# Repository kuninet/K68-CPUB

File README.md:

# K68-CPUB

## 注意!! REV1基板はバグ多数です。REV2基板を使ってください。

* https://kuninet.org/2021/08/16/mc6800-cpu%e3%83%9c%e3%83%bc%e3%83%892-%e3%83%97%e3%83%aa%e3%83%b3%e3%83%88%e5%9f%ba%e6%9d%bf%e5%8c%96/

## 概要

* MC6800を使ったマイコンボードです。
  * MIKBUGオリジナルROMで動きます。
  * PIA MC6821/20をつかったシリアル通信が可能で、300bpsです。
* 10cm x 10cm サイズのプリント基板データがあります。基板固定穴は秋月電子Bサイズユニバーサル基板に合わせてあります。

## 部品・回路図など

* 部品表は以下のディレクトリに入っています。
  * KiCAD/K68-CPUB_BOM/BOM.csv
* 回路図PDFは以下のディレクトリに入っています。
  * KiCAD/K68-CPUB.pdf

## スイッチ、調整方法について
### スイッチ
* 基板上に以下のスイッチがあります。

| 記号 | スイッチ名     | 機能                                          |
| ---- | -------------- | --------------------------------------------- |
| SW1  | 電源スイッチ   | 電源のOFF/ON                                  |
| SW2  | エコーバックSW | 通常はONにして使用してください。              |
| SW3  | ボーレートSW   | 110bps/300bpsの切り替え。<br>ONで300bpsです。 |

### CPUクロック調整、シリアルクロック調整
#### CPUクロック
* 部品を組み付けたのち 74LS123のそばのRV1、RV2を調整して 700kHz～1MHzぐらいに調整してください。
* ※テスタ等の周波数カウンタをGNDとMC6800 CPUのPH1/PH2端子につないで調整してください。

### シリアルクロック
* 部品を組み付けたのち RV3を調整してください。300bpsにする場合は150Hzになるように調整してください。
* ※テスタ等の周波数カウンタをGNDとMC14536の13番ピンにつないで調整してください。

## 参考

* 書籍「マイコンの作り方・使い方」 啓学出版

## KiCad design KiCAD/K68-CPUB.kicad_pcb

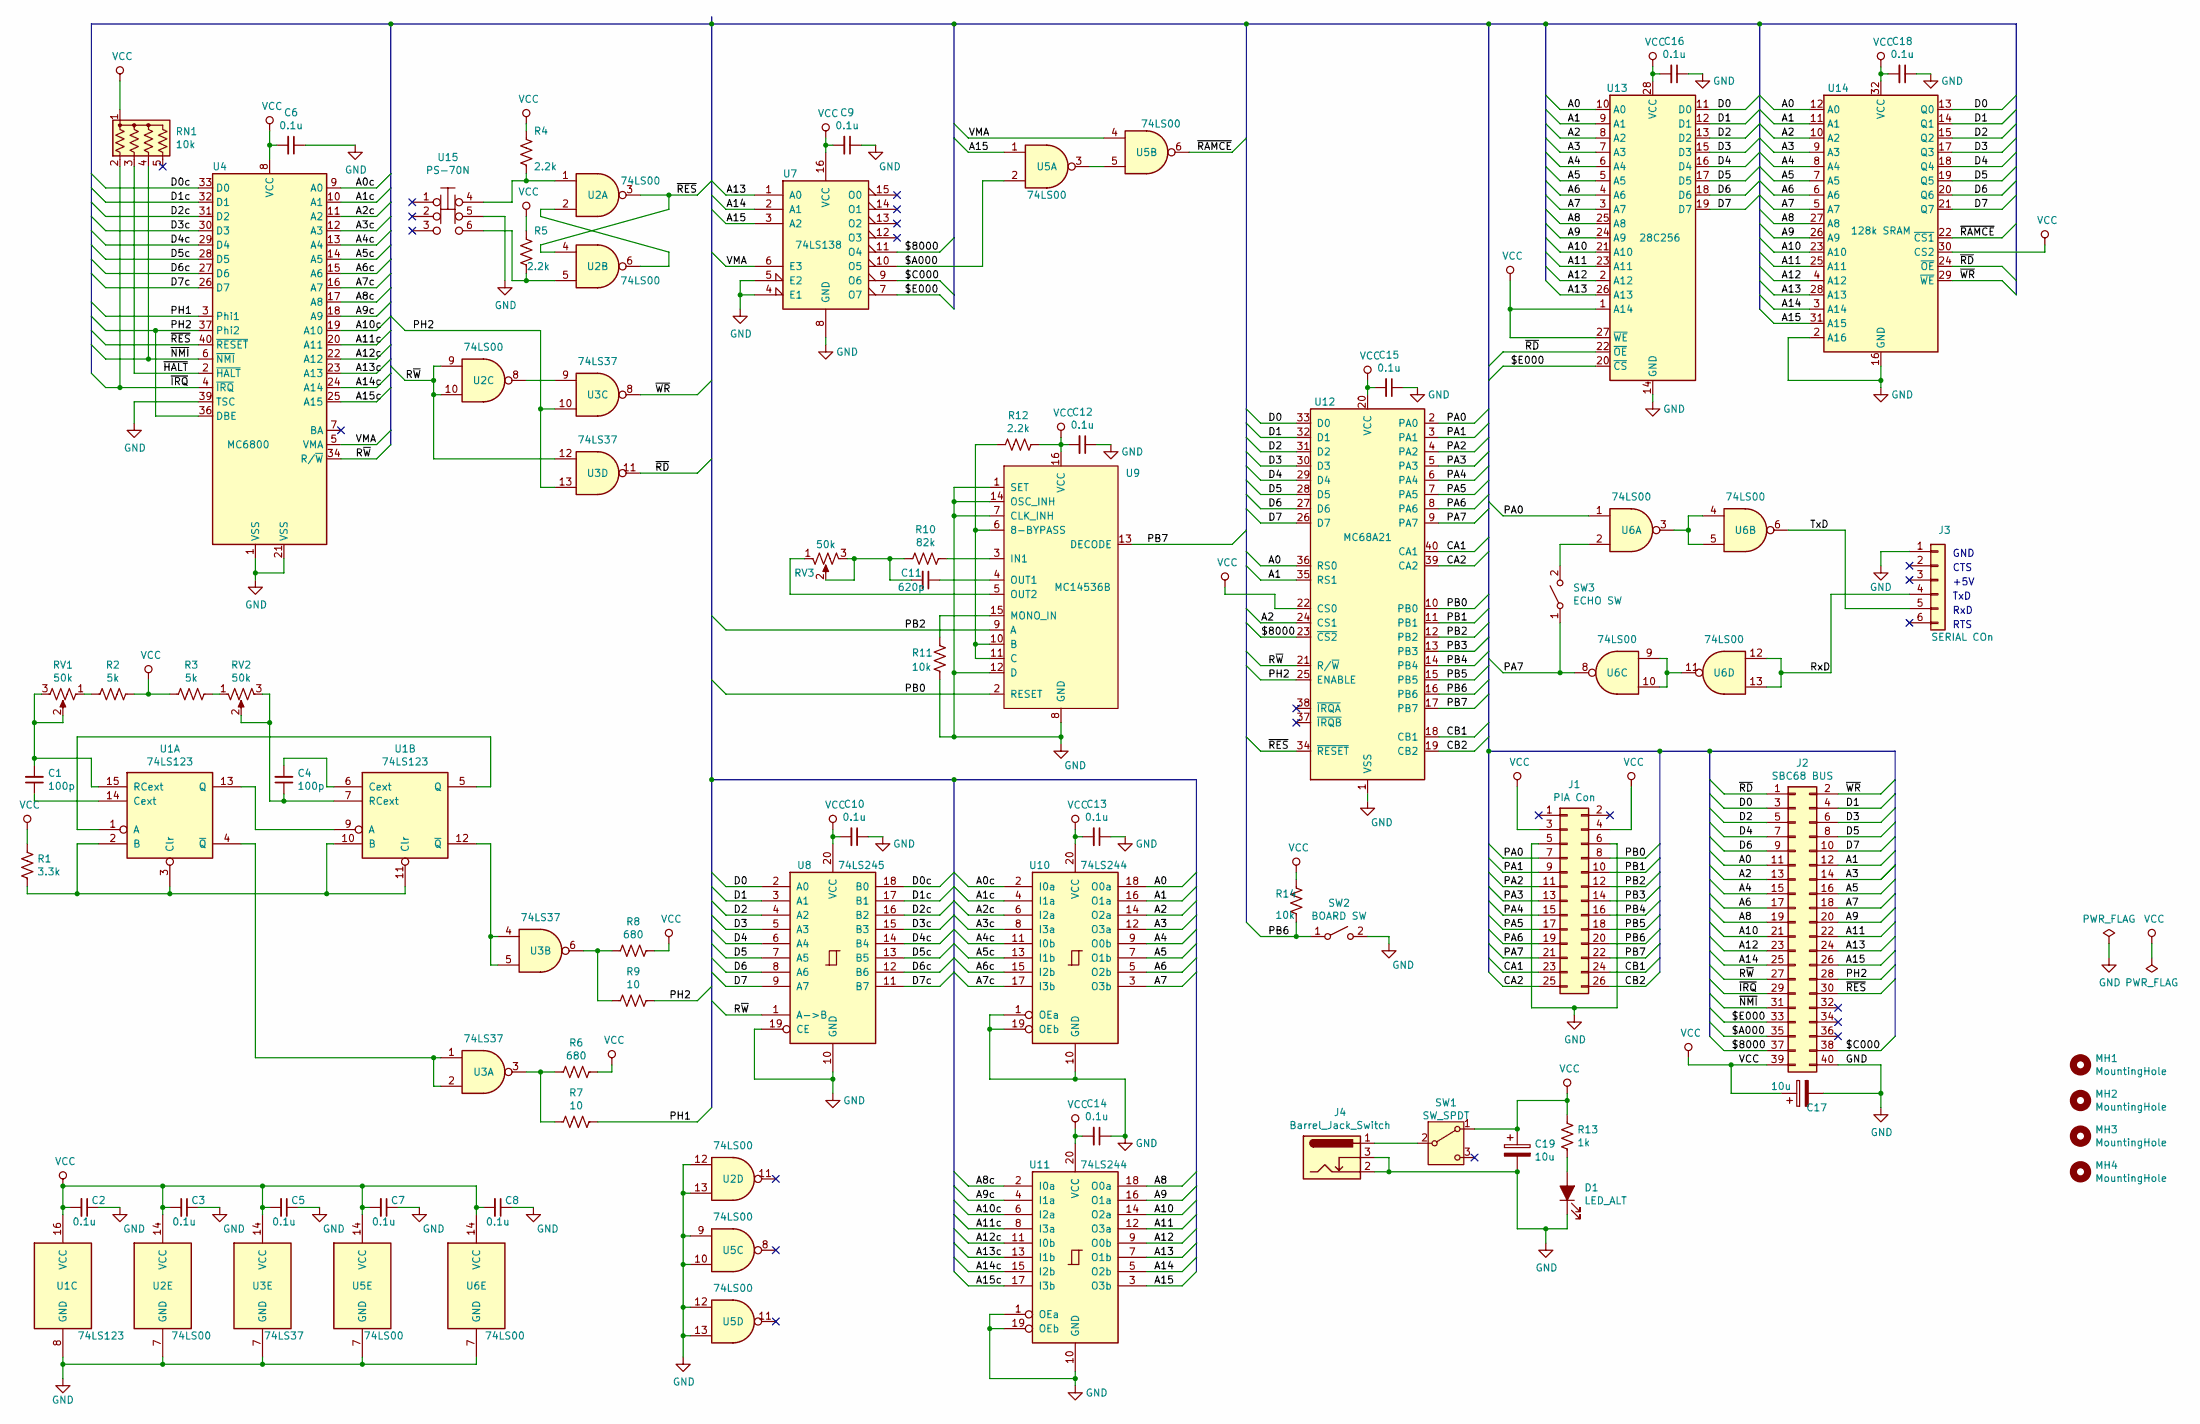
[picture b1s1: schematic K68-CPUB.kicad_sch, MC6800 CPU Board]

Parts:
C1, C4: 100p; C_Disc_D4.3mm_W1.9mm_P5.00mm
C2, C3, C5, C6, C7, C8, C9, C10, C12, C13, C14, C15, C16, C18: 0.1u; C_Disc_D3.0mm_W1.6mm_P2.50mm
C11: 620p; C_Disc_D4.3mm_W1.9mm_P5.00mm
C17, C19: 10u; CP_Radial_D5.0mm_P2.50mm
D1: LED_ALT; LED_D3.0mm
J1: PIA Con; PinHeader_2x13_P2.54mm_Horizontal
J2: SBC68 BUS; PinHeader_2x20_P2.54mm_Horizontal
J3: SERIAL COn; PinHeader_1x06_P2.54mm_Horizontal
J4: Barrel_Jack_Switch; BarrelJack_Horizontal
MH1, MH2, MH3, MH4: MountingHole; MountingHole_3.2mm_M3
R1: 3.3k; R_Axial_DIN0207_L6.3mm_D2.5mm_P10.16mm_Horizontal
R2, R3: 5k; R_Axial_DIN0207_L6.3mm_D2.5mm_P10.16mm_Horizontal
R4, R5, R12: 2.2k; R_Axial_DIN0207_L6.3mm_D2.5mm_P10.16mm_Horizontal
R6, R8: 680; R_Axial_DIN0207_L6.3mm_D2.5mm_P10.16mm_Horizontal
R7, R9: 10; R_Axial_DIN0207_L6.3mm_D2.5mm_P10.16mm_Horizontal
R10: 82k; R_Axial_DIN0207_L6.3mm_D2.5mm_P10.16mm_Horizontal
R11, R14: 10k; R_Axial_DIN0207_L6.3mm_D2.5mm_P10.16mm_Horizontal
R13: 1k; R_Axial_DIN0207_L6.3mm_D2.5mm_P10.16mm_Horizontal
RN1: 10k; R_Array_SIP5
RV1, RV2, RV3: 50k; Potentiometer_Bourns_3386P_Vertical
SW1: SW_SPDT; PinHeader_1x03_P2.54mm_Vertical
SW2: BOARD SW; PinHeader_1x03_P2.54mm_Vertical
SW3: ECHO SW; PinHeader_1x03_P2.54mm_Vertical
U1: 74LS123; DIP-16_W7.62mm_Socket
U2, U5, U6: 74LS00; DIP-14_W7.62mm_Socket
U3: 74LS37; DIP-14_W7.62mm_Socket
U4: MC6800; DIP-40_W15.24mm_Socket
U7: 74LS138; DIP-16_W7.62mm_Socket
U8: 74LS245; DIP-20_W7.62mm_Socket
U9: MC14536B; DIP-16_W7.62mm_Socket
U10, U11: 74LS244; DIP-20_W7.62mm_Socket
U12: MC68A21; DIP-40_W15.24mm_Socket
U13: 28C256; DIP-28_W15.24mm_Socket
U14: 128k SRAM; DIP-32_W15.24mm_Socket
U15: PS-70N; SW_PUSH_PS-70N

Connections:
/$8000: J2.37, U7.11 (O4), U12.23 (~CS2)
/$A000: J2.35, U5.2, U7.10 (O5)
/$C000: J2.38, U7.9 (O6)
/$E000: J2.33, U7.7 (O7), U13.20 (~CS)
/A0: J2.11, U10.18 (O0a), U12.36 (RS0), U13.10 (A0), U14.12 (A0)
/A0c: U4.9 (A0), U10.2 (I0a)
/A1: J2.12, U10.16 (O1a), U12.35 (RS1), U13.9 (A1), U14.11 (A1)
/A1c: U4.10 (A1), U10.4 (I1a)
/A2: J2.13, U10.14 (O2a), U12.24 (CS1), U13.8 (A2), U14.10 (A2)
/A2c: U4.11 (A2), U10.6 (I2a)
/A3: J2.14, U10.12 (O3a), U13.7 (A3), U14.9 (A3)
/A3c: U4.12 (A3), U10.8 (I3a)
/A4: J2.15, U10.9 (O0b), U13.6 (A4), U14.8 (A4)
/A4c: U4.13 (A4), U10.11 (I0b)
/A5: J2.16, U10.7 (O1b), U13.5 (A5), U14.7 (A5)
/A5c: U4.14 (A5), U10.13 (I1b)
/A6: J2.17, U10.5 (O2b), U13.4 (A6), U14.6 (A6)
/A6c: U4.15 (A6), U10.15 (I2b)
/A7: J2.18, U10.3 (O3b), U13.3 (A7), U14.5 (A7)
/A7c: U4.16 (A7), U10.17 (I3b)
/A8: J2.19, U11.18 (O0a), U13.25 (A8), U14.27 (A8)
/A8c: U4.17 (A8), U11.2 (I0a)
/A9: J2.20, U11.16 (O1a), U13.24 (A9), U14.26 (A9)
/A9c: U4.18 (A9), U11.4 (I1a)
/A10: J2.21, U11.14 (O2a), U13.21 (A10), U14.23 (A10)
/A10c: U4.19 (A10), U11.6 (I2a)
/A11: J2.22, U11.12 (O3a), U13.23 (A11), U14.25 (A11)
/A11c: U4.20 (A11), U11.8 (I3a)
/A12: J2.23, U11.9 (O0b), U13.2 (A12), U14.4 (A12)
/A12c: U4.22 (A12), U11.11 (I0b)
/A13: J2.24, U7.1 (A0), U11.7 (O1b), U13.26 (A13), U14.28 (A13)
/A13c: U4.23 (A13), U11.13 (I1b)
/A14: J2.25, U7.2 (A1), U11.5 (O2b), U14.3 (A14)
/A14c: U4.24 (A14), U11.15 (I2b)
/A15: J2.26, U5.1, U7.3 (A2), U11.3 (O3b), U14.31 (A15)
/A15c: U4.25 (A15), U11.17 (I3b)
/CA1: J1.23, U12.40 (CA1)
/CA2: J1.25, U12.39 (CA2)
/CB1: J1.24, U12.18 (CB1)
/CB2: J1.26, U12.19 (CB2)
/D0: J2.3, U8.2 (A0), U12.33 (D0), U13.11 (D0), U14.13 (Q0)
/D0c: U4.33 (D0), U8.18 (B0)
/D1: J2.4, U8.3 (A1), U12.32 (D1), U13.12 (D1), U14.14 (Q1)
/D1c: U4.32 (D1), U8.17 (B1)
/D2: J2.5, U8.4 (A2), U12.31 (D2), U13.13 (D2), U14.15 (Q2)
/D2c: U4.31 (D2), U8.16 (B2)
/D3: J2.6, U8.5 (A3), U12.30 (D3), U13.15 (D3), U14.17 (Q3)
/D3c: U4.30 (D3), U8.15 (B3)
/D4: J2.7, U8.6 (A4), U12.29 (D4), U13.16 (D4), U14.18 (Q4)
/D4c: U4.29 (D4), U8.14 (B4)
/D5: J2.8, U8.7 (A5), U12.28 (D5), U13.17 (D5), U14.19 (Q5)
/D5c: U4.28 (D5), U8.13 (B5)
/D6: J2.9, U8.8 (A6), U12.27 (D6), U13.18 (D6), U14.20 (Q6)
/D6c: U4.27 (D6), U8.12 (B6)
/D7: J2.10, U8.9 (A7), U12.26 (D7), U13.19 (D7), U14.21 (Q7)
/D7c: U4.26 (D7), U8.11 (B7)
/PA0: J1.7, U6.1, U12.2 (PA0)
/PA1: J1.9, U12.3 (PA1)
/PA2: J1.11, U12.4 (PA2)
/PA3: J1.13, U12.5 (PA3)
/PA4: J1.15, U12.6 (PA4)
/PA5: J1.17, U12.7 (PA5)
/PA6: J1.19, U12.8 (PA6)
/PA7: J1.21, SW3.1 (A), U6.8, U12.9 (PA7)
/PB0: J1.8, U9.2 (RESET), U12.10 (PB0)
/PB1: J1.10, U12.11 (PB1)
/PB2: J1.12, U9.9 (A), U12.12 (PB2)
/PB3: J1.14, U12.13 (PB3)
/PB4: J1.16, U12.14 (PB4)
/PB5: J1.18, U12.15 (PB5)
/PB6: J1.20, R14.1, SW2.1 (A), U12.16 (PB6)
/PB7: J1.22, U9.13 (DECODE), U12.17 (PB7)
/PH1: R7.1, U4.3 (Phi1)
/PH2: J2.28, R9.1, U3.10, U3.13, U4.36 (DBE), U4.37 (Phi2), U12.25 (ENABLE)
/RxD: J3.4, U6.12, U6.13
/R~W: J2.27, U2.9, U2.10, U3.12, U4.34 (R/~W), U8.1 (A->B), U12.21 (R/~W)
/TxD: J3.5, U6.6
/VMA: U4.5 (VMA), U5.4, U7.6 (E3)
/~HALT: RN1.3 (R2), U4.2 (~HALT)
/~IRQ: J2.29, RN1.2 (R1), U4.4 (~IRQ)
/~NMI: J2.31, RN1.4 (R3), U4.6 (~NMI)
/~RAMCE: U5.6, U14.22 (~CS1)
/~RD: J2.1, U3.11, U13.22 (~OE), U14.24 (~OE)
/~RES: J2.30, U2.3, U2.4, U4.40 (~RESET), U12.34 (~RESET)
/~WR: J2.2, U3.8, U14.29 (~WE)
GND: C2.1, C3.1, C5.1, C6.1, C7.1, C8.1, C9.1, C10.1, C12.1, C13.1, C14.1, C15.1, C16.1, C17.2, C18.1, C19.2, D1.1 (K), J1.5, J1.6, J2.40, J3.1, J4.2, J4.3, R11.1, SW2.2 (B), U1.8 (GND), U2.7 (GND), U2.12, U2.13, U3.7 (GND), U4.1 (VSS), U4.21 (VSS), U4.39 (TSC), U5.7 (GND), U5.9, U5.10, U5.12, U5.13, U6.7 (GND), U7.4 (E1), U7.5 (E2), U7.8 (GND), U8.10 (GND), U8.19 (CE), U9.1 (SET), U9.7 (CLK_INH), U9.8 (GND), U9.12 (D), U9.14 (OSC_INH), U10.1 (OEa), U10.10 (GND), U10.19 (OEb), U11.1 (OEa), U11.10 (GND), U11.19 (OEb), U12.1 (VSS), U13.14 (GND), U14.2 (A16), U14.16 (GND), U15.5
unnamed: C11.2, R10.2, RV3.2, RV3.3
unnamed: D1.2 (A), R13.2
unnamed: R2.2, RV1.1
unnamed: R3.1, RV2.1
unnamed: R4.2, U2.1, U15.4
unnamed: R5.2, U2.5, U15.6
unnamed: R6.2, R7.2, U3.3
unnamed: R8.2, R9.2, U3.6
unnamed: J4.1, SW1.2 (B)
unnamed: SW3.2 (B), U6.2
unnamed: U1.1 (A), U1.5 (Q)
unnamed: R1.2, U1.2 (B), U1.3 (Clr), U1.10 (B), U1.11 (Clr)
unnamed: C1.1, U1.14 (Cext)
unnamed: U1.9 (A), U1.13 (Q)
unnamed: C1.2, RV1.2, RV1.3, U1.15 (RCext)
unnamed: U1.4 (~Q), U3.1, U3.2
unnamed: C4.2, U1.6 (Cext)
unnamed: C4.1, RV2.2, RV2.3, U1.7 (RCext)
unnamed: U1.12 (~Q), U3.4, U3.5
unnamed: U2.2, U2.6
unnamed: U2.8, U3.9
unnamed: U5.3, U5.5
unnamed: U6.3, U6.4, U6.5
unnamed: U6.9, U6.10, U6.11
unnamed: R12.2, U9.6 (8-BYPASS), U9.10 (B), U9.11 (C)
unnamed: R10.1, U9.3 (IN1)
unnamed: R11.2, U9.15 (MONO_IN)
unnamed: C11.1, U9.4 (OUT1)
unnamed: RV3.1, U9.5 (OUT2)
VCC: C2.2, C3.2, C5.2, C6.2, C7.2, C8.2, C9.2, C10.2, C12.2, C13.2, C14.2, C15.2, C16.2, C17.1, C18.2, C19.1, J1.3, J1.4, J2.39, R1.1, R2.1, R3.2, R4.1, R5.1, R6.1, R8.1, R12.1, R13.1, R14.2, RN1.1 (common), SW1.1 (A), U1.16 (VCC), U2.14 (VCC), U3.14 (VCC), U4.8 (VCC), U5.14 (VCC), U6.14 (VCC), U7.16 (VCC), U8.20 (VCC), U9.16 (VCC), U10.20 (VCC), U11.20 (VCC), U12.20 (VCC), U12.22 (CS0), U13.1 (A14), U13.27 (~WE), U13.28 (VCC), U14.30 (CS2), U14.32 (VCC)

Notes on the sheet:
RxD
+5V
GND
TxD
CTS
RTS

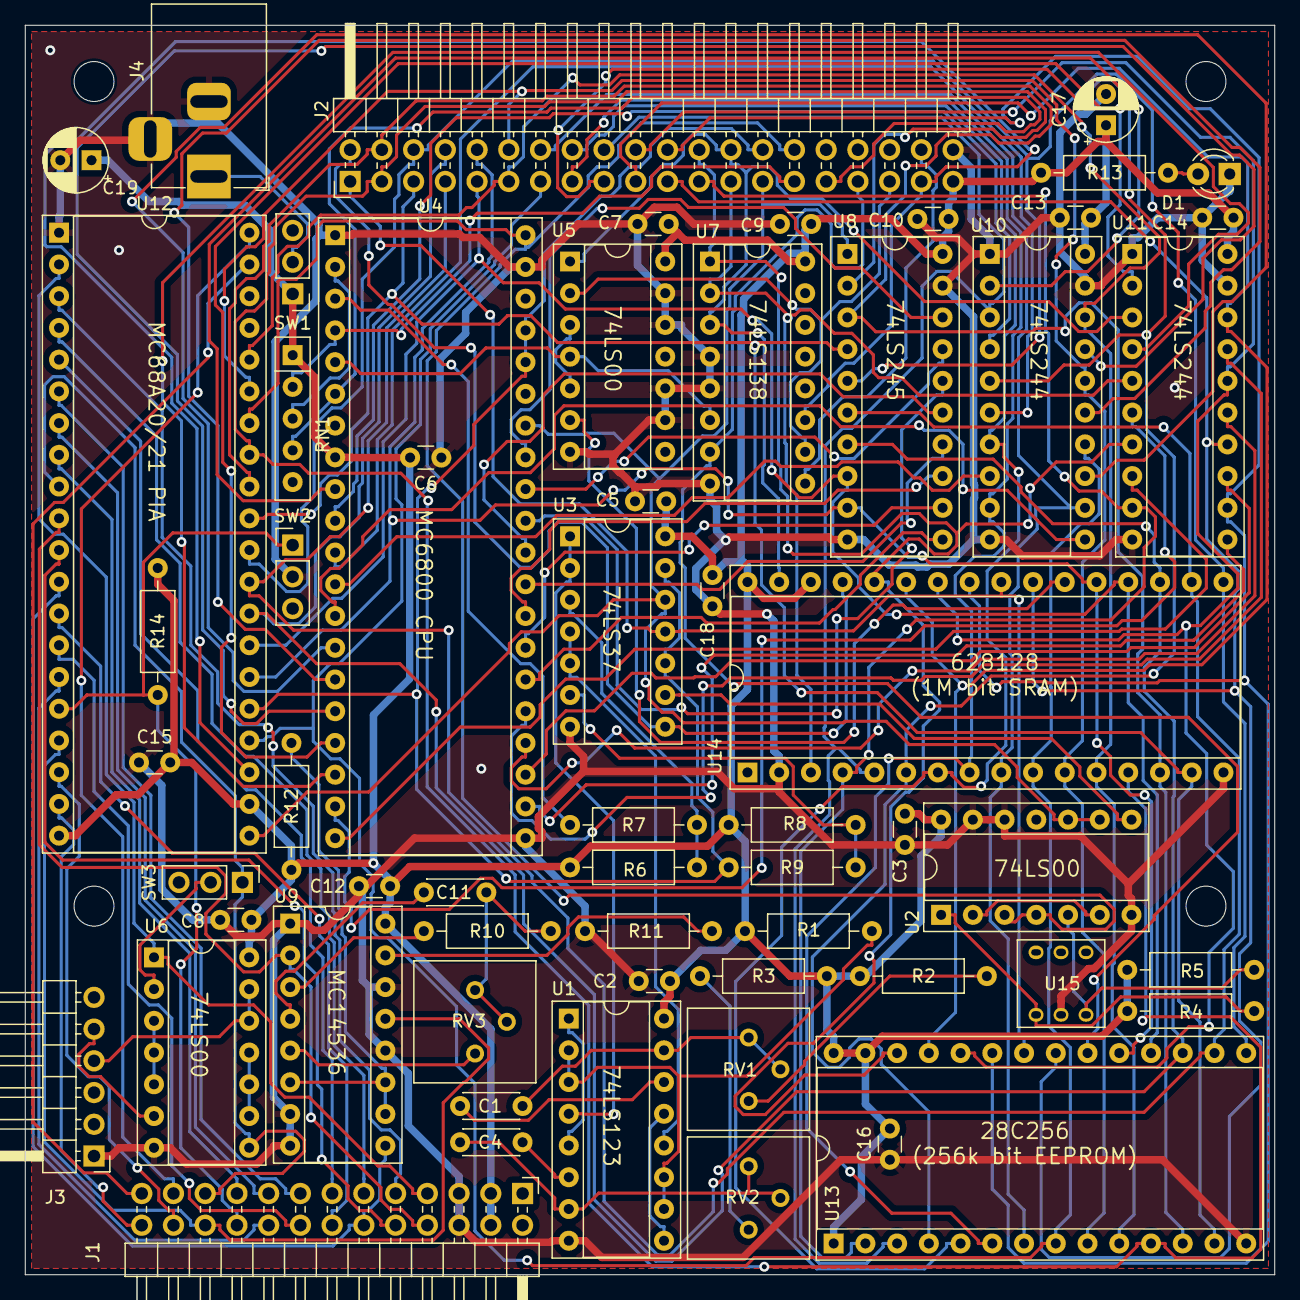
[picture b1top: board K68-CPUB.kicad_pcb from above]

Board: 2 copper layers, 100.0 x 100.0 mm, 64 parts (0 on the bottom side), 116 nets.

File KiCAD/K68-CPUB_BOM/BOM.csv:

Reference, Value, Footprint, Datasheet
C1,100p,Capacitor_THT:C_Disc_D4.3mm_W1.9mm_P5.00mm,~
C2,0.1u,Capacitor_THT:C_Disc_D3.0mm_W1.6mm_P2.50mm,~
C3,0.1u,Capacitor_THT:C_Disc_D3.0mm_W1.6mm_P2.50mm,~
C4,100p,Capacitor_THT:C_Disc_D4.3mm_W1.9mm_P5.00mm,~
C5,0.1u,Capacitor_THT:C_Disc_D3.0mm_W1.6mm_P2.50mm,~
C6,0.1u,Capacitor_THT:C_Disc_D3.0mm_W1.6mm_P2.50mm,~
C7,0.1u,Capacitor_THT:C_Disc_D3.0mm_W1.6mm_P2.50mm,~
C8,0.1u,Capacitor_THT:C_Disc_D3.0mm_W1.6mm_P2.50mm,~
C9,0.1u,Capacitor_THT:C_Disc_D3.0mm_W1.6mm_P2.50mm,~
C10,0.1u,Capacitor_THT:C_Disc_D3.0mm_W1.6mm_P2.50mm,~
C11,620p,Capacitor_THT:C_Disc_D4.3mm_W1.9mm_P5.00mm,~
C12,0.1u,Capacitor_THT:C_Disc_D3.0mm_W1.6mm_P2.50mm,~
C13,0.1u,Capacitor_THT:C_Disc_D3.0mm_W1.6mm_P2.50mm,~
C14,0.1u,Capacitor_THT:C_Disc_D3.0mm_W1.6mm_P2.50mm,~
C15,0.1u,Capacitor_THT:C_Disc_D3.0mm_W1.6mm_P2.50mm,~
C16,0.1u,Capacitor_THT:C_Disc_D3.0mm_W1.6mm_P2.50mm,~
C17,10u,Capacitor_THT:CP_Radial_D5.0mm_P2.50mm,~
C18,0.1u,Capacitor_THT:C_Disc_D3.0mm_W1.6mm_P2.50mm,~
C19,10u,Capacitor_THT:CP_Radial_D5.0mm_P2.50mm,~
D1,LED_ALT,LED_THT:LED_D3.0mm,~
J1,PIA Con,Connector_PinHeader_2.54mm:PinHeader_2x13_P2.54mm_Horizontal,~
J2,SBC68 BUS,Connector_PinHeader_2.54mm:PinHeader_2x20_P2.54mm_Horizontal,~
J3,SERIAL COn,Connector_PinHeader_2.54mm:PinHeader_1x06_P2.54mm_Horizontal,~
J4,Barrel_Jack_Switch,Connector_BarrelJack:BarrelJack_Horizontal,~
R1,3.3k,Resistor_THT:R_Axial_DIN0207_L6.3mm_D2.5mm_P10.16mm_Horizontal,~
R2,5k,Resistor_THT:R_Axial_DIN0207_L6.3mm_D2.5mm_P10.16mm_Horizontal,~
R3,5k,Resistor_THT:R_Axial_DIN0207_L6.3mm_D2.5mm_P10.16mm_Horizontal,~
R4,2.2k,Resistor_THT:R_Axial_DIN0207_L6.3mm_D2.5mm_P10.16mm_Horizontal,~
R5,2.2k,Resistor_THT:R_Axial_DIN0207_L6.3mm_D2.5mm_P10.16mm_Horizontal,~
R6,680,Resistor_THT:R_Axial_DIN0207_L6.3mm_D2.5mm_P10.16mm_Horizontal,~
R7,10,Resistor_THT:R_Axial_DIN0207_L6.3mm_D2.5mm_P10.16mm_Horizontal,~
R8,680,Resistor_THT:R_Axial_DIN0207_L6.3mm_D2.5mm_P10.16mm_Horizontal,~
R9,10,Resistor_THT:R_Axial_DIN0207_L6.3mm_D2.5mm_P10.16mm_Horizontal,~
R10,82k,Resistor_THT:R_Axial_DIN0207_L6.3mm_D2.5mm_P10.16mm_Horizontal,~
R11,10k,Resistor_THT:R_Axial_DIN0207_L6.3mm_D2.5mm_P10.16mm_Horizontal,~
R12,2.2k,Resistor_THT:R_Axial_DIN0207_L6.3mm_D2.5mm_P10.16mm_Horizontal,~
R13,1k,Resistor_THT:R_Axial_DIN0207_L6.3mm_D2.5mm_P10.16mm_Horizontal,~
R14,10k,Resistor_THT:R_Axial_DIN0207_L6.3mm_D2.5mm_P10.16mm_Horizontal,~
RN1,10k,Resistor_THT:R_Array_SIP5,http://www.vishay.com/docs/31509/csc.pdf
RV1,50k,Potentiometer_THT:Potentiometer_Bourns_3386P_Vertical,~
RV2,50k,Potentiometer_THT:Potentiometer_Bourns_3386P_Vertical,~
RV3,50k,Potentiometer_THT:Potentiometer_Bourns_3386P_Vertical,~
SW1,SW_SPDT,Connector_PinHeader_2.54mm:PinHeader_1x03_P2.54mm_Vertical,~
SW2,BOARD SW,Connector_PinHeader_2.54mm:PinHeader_1x03_P2.54mm_Vertical,~
SW3,ECHO SW,Connector_PinHeader_2.54mm:PinHeader_1x03_P2.54mm_Vertical,~
U1,74LS123,Package_DIP:DIP-16_W7.62mm_Socket,http://www.ti.com/lit/gpn/sn74LS123
U2,74LS00,Package_DIP:DIP-14_W7.62mm_Socket,http://www.ti.com/lit/gpn/sn74ls00
U3,74LS37,Package_DIP:DIP-14_W7.62mm_Socket,http://www.ti.com/lit/gpn/sn74ls00
U4,MC6800,Package_DIP:DIP-40_W15.24mm_Socket,http://pdf.datasheetcatalog.com/datasheet/motorola/MC68A00L.pdf
U5,74LS00,Package_DIP:DIP-14_W7.62mm_Socket,http://www.ti.com/lit/gpn/sn74ls00
U6,74LS00,Package_DIP:DIP-14_W7.62mm_Socket,http://www.ti.com/lit/gpn/sn74ls00
U7,74LS138,Package_DIP:DIP-16_W7.62mm_Socket,http://www.ti.com/lit/gpn/sn74LS138
U8,74LS245,Package_DIP:DIP-20_W7.62mm_Socket,http://www.ti.com/lit/gpn/sn74LS245
U9,MC14536B,Package_DIP:DIP-16_W7.62mm_Socket,
U10,74LS244,Package_DIP:DIP-20_W7.62mm_Socket,http://www.ti.com/lit/gpn/sn74LS244
U11,74LS244,Package_DIP:DIP-20_W7.62mm_Socket,http://www.ti.com/lit/gpn/sn74LS244
U12,MC68A21,Package_DIP:DIP-40_W15.24mm_Socket,http://pdf.datasheetcatalog.com/datasheet/motorola/6821.pdf
U13,28C256,Package_DIP:DIP-28_W15.24mm_Socket,http://ww1.microchip.com/downloads/en/DeviceDoc/doc0006.pdf
U14,128k SRAM,Package_DIP:DIP-32_W15.24mm_Socket,http://www.futurlec.com/Datasheet/Memory/628128.pdf
U15,PS-70N,PUSH_SW:SW_PUSH_PS-70N,

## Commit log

2021-07-25 init commit
2021-07-25 README等作成
2021-07-25 Create LICENSE
2021-07-25 ガーバーデータ(仮) 生成
2021-07-25 基板イメージ追加
2021-07-25 基板裏面シルク追加・ガーバーデータ再作成
2024-04-21 回路バグ修正
2024-04-21 基板パターン修正中...
2024-04-21 REV2 基板 ガーバー出力
2025-04-05 ビアのテンティングを変更してREV2ガーバー再出力
2025-04-13 回路図REV2版PDF出力
2025-04-13 READMEにスイッチやクロック調整方法追記
